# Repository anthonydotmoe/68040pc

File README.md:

# 68040pc

Welcome to the `68040pc` (working name) project, an ambitious endeavor to build
a general-purpose computer platform powered by the Motorola 68040 (or, in this
case, the 68LC040) CPU. Inspired by creations like Ben Eater's breadboard 6502
computer and me finding a 68LC040 in a bin, this project seeks to bring the
charm of vintage computing into the modern era with a twist of power and
utility. Call me crazy, but I expect to be able to use this machine when it's
done.

## Status

The `testboard` design is almost complete. I'm going to sleep on the design
before ordering boards. The FPGA does address decoding and interrupt
management and will contain a sound core to output some cool beeps through
the I2S DAC module. I'm pleased with how the project is going so far!

## Objectives

The `68040pc` aims to be versatile and user-friendly, with the following
capabilities:
- **Input/Output**: Support for keyboard (text input) and mouse for GUI
  interactions.
- **Display**: Text display for command-line operations and a graphics display
  ready for GUI applications.
- **Storage**: Compatibility with standard bulk storage devices, including
  floppies and hard drives.
- **OS**: Capability to run a preemptive multitasking operating system.
- **Expansion**: A robust expansion system, ensuring the platform remains
  relevant and adaptable after its initial production.

## Performance Expectations

With the integration of the 68040 CPU and the potential to accommodate up to
512MB of RAM, I anticipate the `68040pc` will rival the performance metrics of
systems like the Amiga, especially in terms of computational power. Although the
base system might not match the Amiga's graphical prowess, there's potential for
future enhancements via expansion cards to bring it to that level.

## Learning and Documentation

This journey isn't just about creating a new machine—it's a significant learning
curve for me, and I want it to serve as an educational resource for others.
Every step of the way, the system will be meticulously documented. From design
decisions to implementation nuances, the goal is to demystify the process and
make the knowledge accessible to all.

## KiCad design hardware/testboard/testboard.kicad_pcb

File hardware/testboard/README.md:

# Errata

* MC68150's TA line is *not* open-collector! Another 74LVC1G08 AND gate should
be used to connect FPGA TA and MC68150 TA to the CPU's TA.

* U802A schematic pin markings are incorrect. At the FPGA, the following changes
need to be made:
    - LV\_SIZ1 -> R/W
    - LV\_SIZ0 -> LV\_SIZ0
    - R/W -> LV\_SIZ1

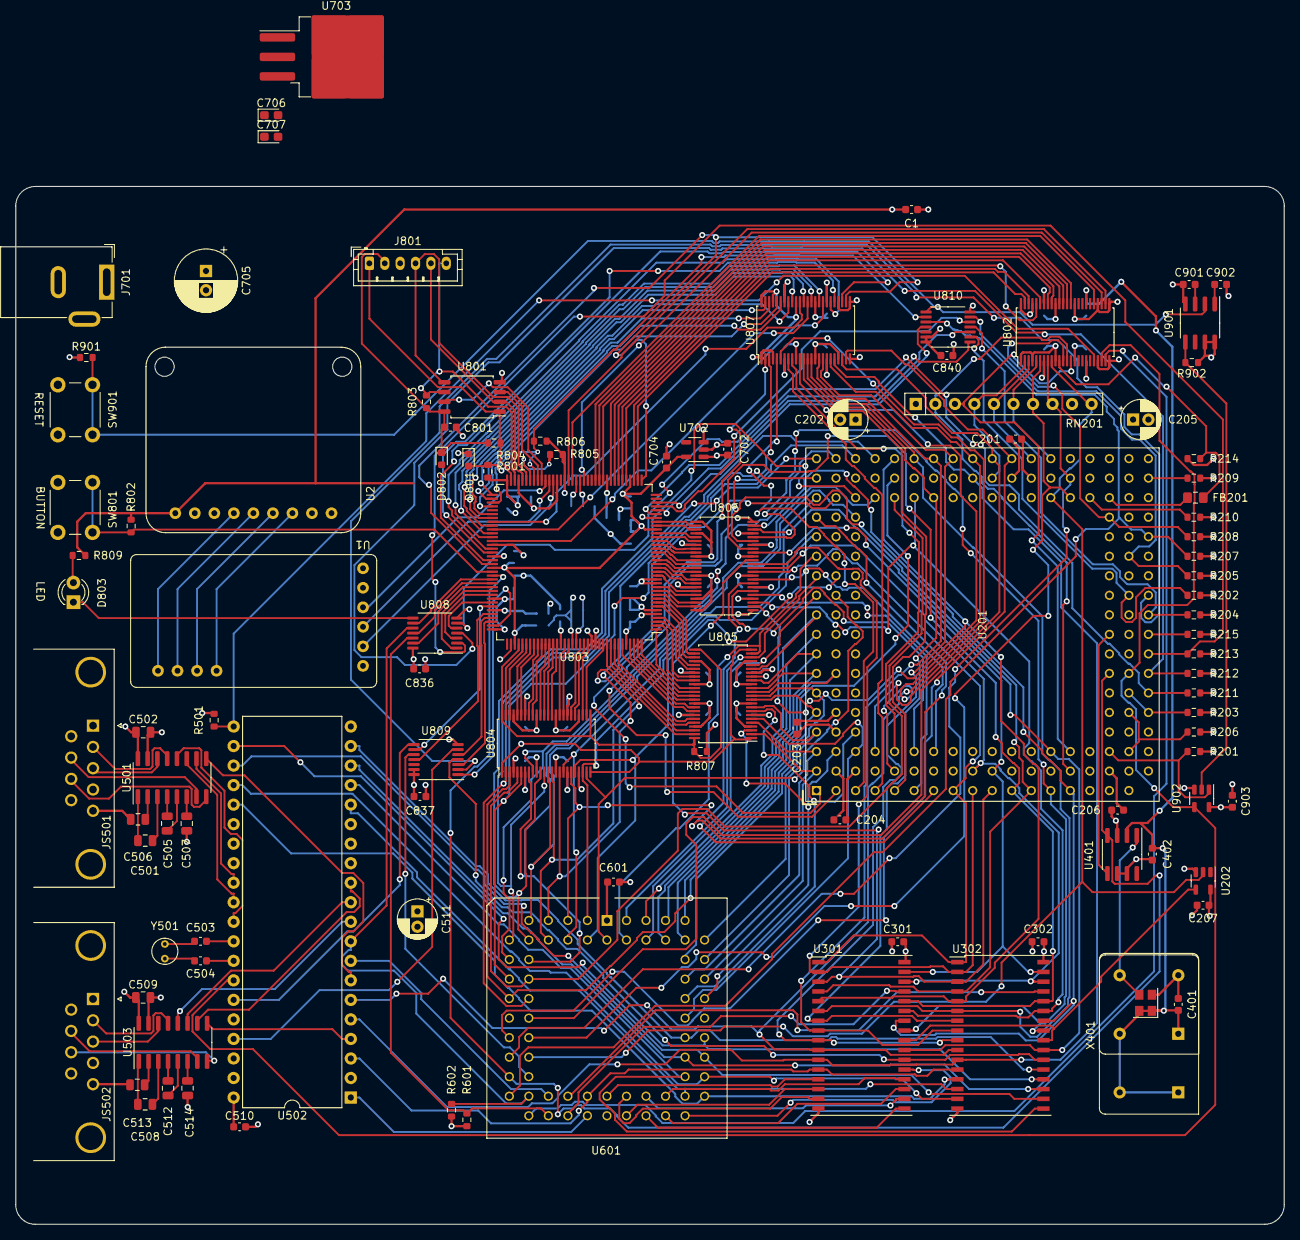
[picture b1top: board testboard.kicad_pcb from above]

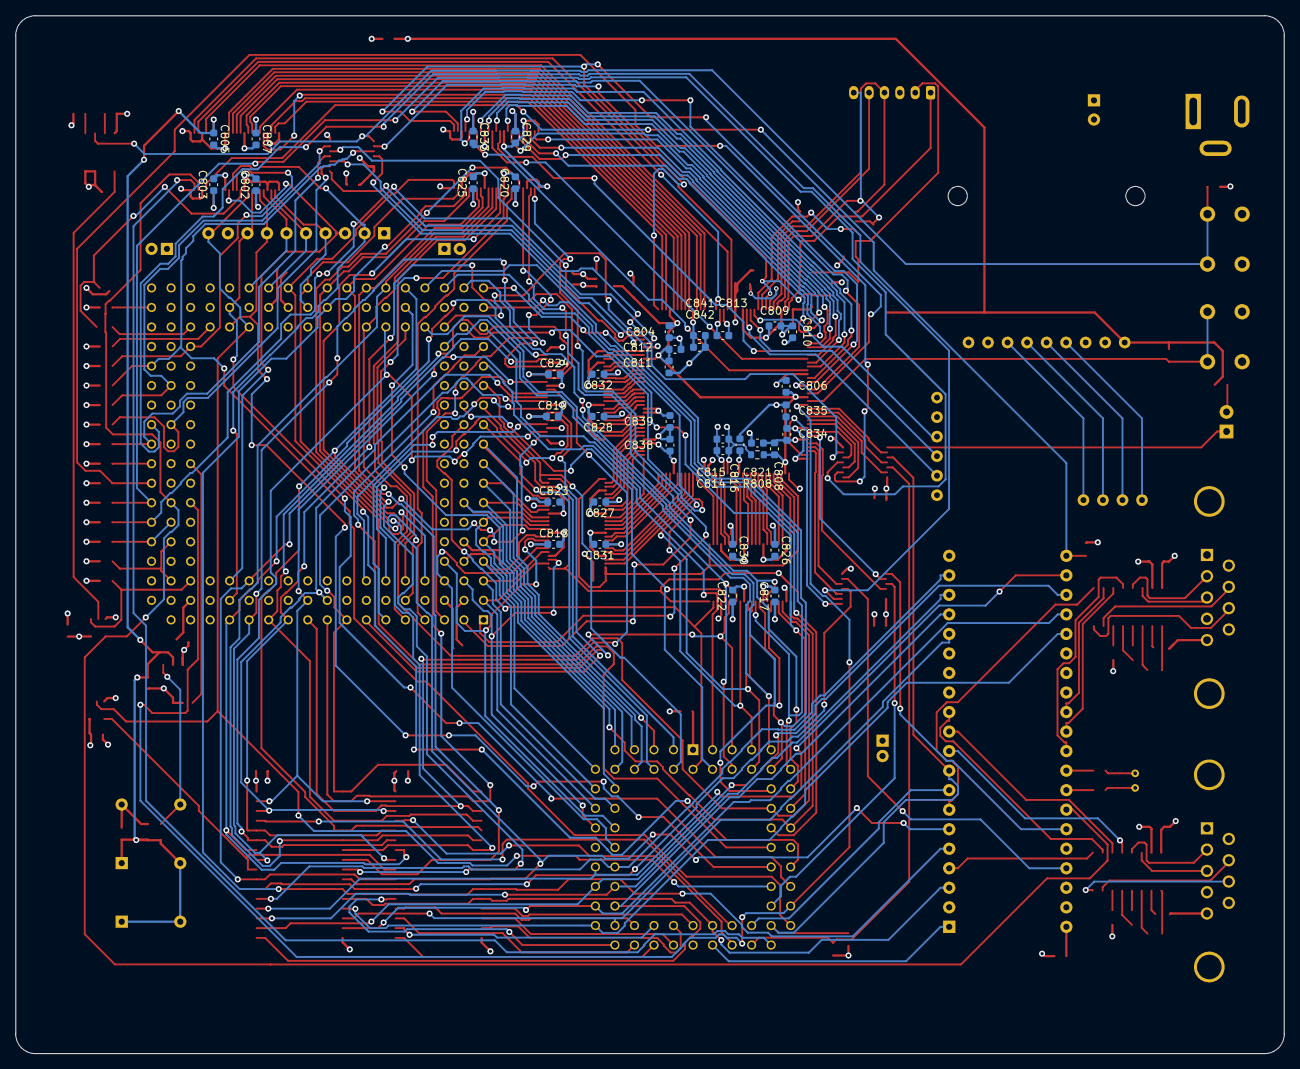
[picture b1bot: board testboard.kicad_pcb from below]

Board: 4 copper layers, 165.0 x 135.0 mm, 146 parts (39 on the bottom side), 278 nets.

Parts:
C1, C702, C704, C809, C812, C815, C821, C835, C839, C842: 4.7uF; C_0603_1608Metric
C201, C204: 0.22uF; C_0603_1608Metric
C202, C205: 22uF; CP_Radial_D5.0mm_P2.00mm
C203, C206: 220pF; C_0603_1608Metric
C207, C301, C302, C401, C402, C510, C601, C801, C802, C803, C804, C805, C806, C807, C808, C810, C811, C813, C814, C816, C817, C818, C819, C820, C822, C823, C824, C825, C826, C827, C828, C829, C830, C831, C832, C833, C834, C836, C837, C838, C840, C841, C901, C902, C903: 100nF; C_0603_1608Metric
C501, C502, C505, C506, C507, C508, C509, C512, C513, C514: 1uF; C_0805_2012Metric
C503, C504: 15pF; C_0603_1608Metric
C511: C_Polarized_Small_US; CP_Radial_D5.0mm_P2.00mm
C705: 220uF; CP_Radial_D8.0mm_P2.50mm
C706: 22uF; CP_EIA-2012-12_Kemet-R
C707: 10uF; CP_EIA-2012-12_Kemet-R
D801: LTST-C191KGKT; LED_0603_1608Metric
D802: D_Schottky; D_0603_1608Metric
D803: LED; LED_D3.0mm
FB201: FerriteBead; L_0805_2012Metric_Pad1.15x1.40mm_HandSolder
J701: Barrel_Jack; BarrelJack_GCT_DCJ200-10-A_Horizontal
J801: Conn_01x06; JST_PH_B6B-PH-K_1x06_P2.00mm_Vertical
JS501, JS502: DE9_Plug_MountingHoles; DSUB-9_Male_Horizontal_P2.77x2.84mm_EdgePinOffset4.94mm_Hou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
R201, R202, R203, R204, R205, R206, R207, R208, R209, R210, R211, R212, R213, R214, R215: 4.7k; R_0603_1608Metric
R501, R601, R602, R802, R901, R902: 1k; R_0603_1608Metric
R801, R809: 2.2K; R_0603_1608Metric
R803, R804: 10K; R_0603_1608Metric
R805, R806: 10k; R_0603_1608Metric
R807: R_Small_US; R_0603_1608Metric
R808: 100; R_0603_1608Metric
RN201: 1k; R_Array_SIP10
SW801: BUTTON; SW_PUSH_6mm
SW901: RESET; SW_PUSH_6mm
U1: DACMOD
U2: MAX98306 Amp; AMP
U201: 68LC040; PGA179
U202: 74LVC1G04; SOT-23-5
U301, U302: IS61C5128AS-25TLI; TSOP-II-32_21.0x10.2mm_P1.27mm
U401: NB3N502; SOIC-8_3.9x4.9mm_P1.27mm
U501, U503: MAX232; SOIC-16_3.9x9.9mm_P1.27mm
U502: 68681; DIP-40_W15.24mm
U601: PLCC-68_THT-Socket
U702: AP2112K-1.2; SOT-23-5
U703: LT1084-3.3; TO-263-3_TabPin2
U801: SST26VF023BA; SOP-8_5.28x5.23mm_P1.27mm
U802, U804, U805, U806, U807: SN74ALVC164245; TSSOP-48_6.1x12.5mm_P0.5mm
U803: ICE40HX4K-TQ144; TQFP-144_20x20mm_P0.5mm
U808, U810: SN74LVC07; TSSOP-14_4.4x5mm_P0.65mm
U809: 74AHCT04; TSSOP-14_4.4x5mm_P0.65mm
U901: TL7705A; SOIC-8_3.9x4.9mm_P1.27mm
U902: 74LVC1G08; SOT-23-5
X401: ASE-33MHz; Oscillator_SMD_Abracon_ASE-4Pin_3.2x2.5mm
X402: 33MHz; Oscillator_DIP-14
X403: 33MHz; Oscillator_DIP-8
Y501: 3.6864MHz; Crystal_C38-LF_D3.0mm_L8.0mm_Vertical

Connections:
+1V2: C704.1, C804.1, C806.1, C808.1, C811.1, C812.1, R808.2, U702.5 (VOUT), U803.27 (VCC), U803.40 (VCC), U803.92 (VCC), U803.111 (VCC)
+3.3V: C1.1, C401.1, C402.1, C706.1, C805.1, C807.1, C809.1, C810.1, C816.1, C821.1, C826.1, C827.1, C828.1, C829.1, C830.1, C831.1, C832.1, C833.1, C834.1, C835.1, C836.1, C838.1, C839.1, C840.1, C841.1, C842.1, D802.2 (A), R801.2, R802.1, R805.1, R806.1, R807.1, R809.2, U1.1 (VIN), U2.1 (V_{DD}), U401.2 (VDD), U703.2 (VO), U802.31 (VCCA), U802.42 (VCCA), U803.6 (VCCIO_3), U803.30 (VCCIO_3), U803.46 (VCCIO_2), U803.57 (VCCIO_2), U803.72 (VCC_SPI), U803.89 (VCCIO_1), U803.100 (VCCIO_1), U803.108 (VPP_2V5), U803.123 (VCCIO_0), U803.131 (VCCIO_0), U804.31 (VCCA), U804.42 (VCCA), U805.31 (VCCA), U805.42 (VCCA), U806.31 (VCCA), U806.42 (VCCA), U807.31 (VCCA), U807.42 (VCCA), U808.14 (VCC), U810.13, U810.14 (VCC), X401.1 (EN), X401.4 (Vdd), X402.1 (EN), X402.14 (Vcc), X403.1 (EN), X403.8 (Vcc)
+5V: C201.1, C202.1, C203.1, C204.1, C205.1, C206.1, C207.1, C301.1, C302.1, C502.1, C509.1, C510.1, C511.1, C601.1, C702.1, C705.1, C707.1, C802.1, C803.1, C817.1, C818.1, C819.1, C820.1, C822.1, C823.1, C824.1, C825.1, C837.1, C903.1, J701.1, R201.1, R202.1, R203.1, R204.1, R205.1, R206.1, R207.1, R208.1, R209.1, R210.1, R211.1, R212.1, R213.1, R214.1, R215.1, R501.1, R601.1, R602.1, R901.1, R902.1, RN201.1 (common), U201.B5 (V_{CC}), U201.B9 (V_{CC}), U201.B14 (V_{CC}), U201.C2 (V_{CC}), U201.C5 (V_{CC}), U201.C8 (V_{CC}), U201.C10 (V_{CC}), U201.C12 (V_{CC}), U201.C14 (V_{CC}), U201.C17 (V_{CC}), U201.G2 (V_{CC}), U201.G17 (V_{CC}), U201.H3 (V_{CC}), U201.H16 (V_{CC}), U201.J3 (V_{CC}), U201.J16 (V_{CC}), U201.L16 (V_{CC}), U201.M2 (V_{CC}), U201.M3 (V_{CC}), U201.M17 (V_{CC}), U201.R2 (V_{CC}), U201.R5 (V_{CC}), U201.R8 (V_{CC}), U201.R12 (V_{CC}), U201.R17 (V_{CC}), U201.S8 (V_{CC}), U201.S16 (V_{CC}), U202.5 (VCC), U301.32 (VDD), U302.32 (VDD), U501.16 (VCC), U502.40 (VCC), U503.16 (VCC), U601.1 (V_{CC}), U601.35 (V_{CC}), U702.1 (VIN), U702.3 (EN), U703.3 (VI), U802.7 (VCCB), U802.18 (VCCB), U804.7 (VCCB), U804.18 (VCCB), U805.7 (VCCB), U805.18 (VCCB), U806.7 (VCCB), U806.18 (VCCB), U807.7 (VCCB), U807.18 (VCCB), U809.13, U809.14 (VCC), U901.7 (SENSE), U901.8 (VCC), U902.5 (VCC)
/A0: U201.L18 (A0), U601.20 (A0), U807.23 (2B8)
/A1: U201.K18 (A1), U601.19 (A1), U807.22 (2B7)
/A2: U201.J17 (A2), U301.11 (A1), U302.11 (A1), U502.5 (RS3), U807.20 (2B6)
/A3: U201.J18 (A3), U301.10 (A2), U302.10 (A2), U502.6 (RS4), U807.19 (2B5)
/A4: U201.H18 (A4), U301.9 (A3), U302.9 (A3), U807.17 (2B4)
/A5: U201.G18 (A5), U301.8 (A4), U302.8 (A4), U807.16 (2B3)
/A6: U201.G16 (A6), U301.7 (A5), U302.7 (A5), U807.13 (2B1)
/A7: U201.F18 (A7), U301.6 (A6), U302.6 (A6), U807.14 (2B2)
/A8: U201.E18 (A8), U301.5 (A7), U302.5 (A7), U806.2 (1B1)
/A9: U201.F16 (A9), U301.27 (A8), U302.27 (A8), U806.3 (1B2)
/A10: U201.P1 (A10), U301.26 (A9), U302.26 (A9), U806.23 (2B8)
/A11: U201.N3 (A11), U301.23 (A10), U302.23 (A10), U806.22 (2B7)
/A12: U201.N1 (A12), U301.25 (A11), U302.25 (A11), U806.20 (2B6)
/A13: U201.M1 (A13), U301.4 (A12), U302.4 (A12), U806.19 (2B5)
/A14: U201.L1 (A14), U301.28 (A13), U302.28 (A13), U806.17 (2B4)
/A15: U201.K1 (A15), U301.3 (A14), U302.3 (A14), U806.14 (2B2)
/A16: U201.K2 (A16), U301.31 (A15), U302.31 (A15), U806.16 (2B3)
/A17: U201.J1 (A17), U301.2 (A16), U302.2 (A16), U806.13 (2B1)
/A18: U201.H1 (A18), U301.1 (A17), U302.1 (A17), U806.11 (1B7)
/A19: U201.J2 (A19), U301.30 (A18), U302.30 (A18), U806.12 (1B8)
/A20: U201.G1 (A20), U806.8 (1B5)
/A21: U201.F1 (A21), U806.5 (1B3)
/A22: U201.E1 (A22), U807.12 (1B8)
/A23: U201.G3 (A23), U806.9 (1B6)
/A24: U201.D1 (A24), U807.8 (1B5)
/A25: U201.F3 (A25), U806.6 (1B4)
/A26: U201.E2 (A26), U807.11 (1B7)
/A27: U201.C1 (A27), U807.5 (1B3)
/A28: U201.E3 (A28), U807.9 (1B6)
/A29: U201.B1 (A29), U807.3 (1B2)
/A30: U201.D3 (A30), U807.6 (1B4)
/A31: U201.A1 (A31), U807.2 (1B1)
/BCLK: U201.R7 (BCLK), U401.4 (REF), U601.24 (BCLK), U803.94 (IOR_141_GBIN2)
/CPU/DLE: R215.2, U201.T9 (JS0)
/CPU/PCLK: U201.R9 (PCLK), U401.5 (CLKOUT)
/CPU/~BB: R209.2, U201.T17 (~BB)
/CPU/~MI: R210.2, U201.Q16 (~MI)
/Clock/CLK33: U401.1 (X1/CLK), X401.3 (OUT), X403.5 (OUT)
/D0: U201.C3 (D0), U601.53 (D0), U805.6 (1B4)
/D1: U201.B3 (D1), U601.54 (D1), U805.3 (1B2)
/D2: U201.C4 (D2), U601.55 (D2), U805.8 (1B5)
/D3: U201.A2 (D3), U601.56 (D3), U805.2 (1B1)
/D4: U201.A3 (D4), U601.57 (D4), U805.5 (1B3)
/D5: U201.A4 (D5), U601.58 (D5), U805.9 (1B6)
/D6: U201.A5 (D6), U601.59 (D6), U805.11 (1B7)
/D7: U201.A6 (D7), U601.60 (D7), U805.12 (1B8)
/D8: U201.B7 (D8), U601.61 (D8), U805.13 (2B1)
/D9: U201.A7 (D9), U601.62 (D9), U805.14 (2B2)
/D10: U201.A8 (D10), U601.63 (D10), U805.16 (2B3)
/D11: U201.A9 (D11), U601.64 (D11), U805.17 (2B4)
/D12: U201.A10 (D12), U601.65 (D12), U805.19 (2B5)
/D13: U201.A11 (D13), U601.66 (D13), U805.20 (2B6)
/D14: U201.A12 (D14), U601.67 (D14), U805.22 (2B7)
/D15: U201.A13 (D15), U601.68 (D15), U805.23 (2B8)
/D16: U201.B11 (D16), U601.2 (D16), U804.23 (2B8)
/D17: U201.A14 (D17), U601.3 (D17), U804.22 (2B7)
/D18: U201.B12 (D18), U601.4 (D18), U804.20 (2B6)
/D19: U201.A15 (D19), U601.5 (D19), U804.19 (2B5)
/D20: U201.A16 (D20), U601.6 (D20), U804.17 (2B4)
/D21: U201.A17 (D21), U601.7 (D21), U804.16 (2B3)
/D22: U201.B16 (D22), U601.8 (D22), U804.14 (2B2)
/D23: U201.C15 (D23), U601.9 (D23), U804.13 (2B1)
/D24: U201.A18 (D24), U601.10 (D24), U804.12 (1B8)
/D25: U201.C16 (D25), U601.11 (D25), U804.11 (1B7)
/D26: U201.B18 (D26), U601.12 (D26), U804.9 (1B6)
/D27: U201.D16 (D27), U601.13 (D27), U804.8 (1B5)
/D28: U201.C18 (D28), U601.14 (D28), U804.6 (1B4)
/D29: U201.E16 (D29), U601.15 (D29), U804.5 (1B3)
/D30: U201.E17 (D30), U601.16 (D30), U804.3 (1B2)
/D31: U201.D18 (D31), U601.17 (D31), U804.2 (1B1)
/FPGA/CDONE: D801.2 (A), R801.1, R806.2, U803.65 (CDONE), U810.9
/FPGA/FLASH_IO2: U801.3 (~WP/SIO2), U803.64 (IOB_104_CBSEL1)
/FPGA/FLASH_IO3: U801.7 (~HOLD/SIO3), U803.63 (IOB_103_CBSEL0)
/FPGA/FLASH_MISO: J801.5, U801.2 (SO/SIO1), U803.68 (IOB_106_SDI)
/FPGA/FLASH_MOSI: J801.4, U801.5 (SI/SIO0), U803.67 (IOB_105_SDO)
/FPGA/FLASH_POWER: C801.1, D802.1 (K), J801.2, R803.2, R804.2, U801.8 (VCC)
/FPGA/FLASH_SCK: J801.6, R803.1, U801.6 (SCLK), U803.70 (IOB_107_SCK)
/FPGA/FLASH_SS: J801.1, R804.1, U801.1 (~CS), U803.71 (IOB_108_SS)
/FPGA/FPGA_BTN: R802.2, SW801.2, U803.93 (IOR_140_GBIN3)
/FPGA/FPGA_D_DIR: U803.110 (IOT_168), U804.1 (1DIR), U804.24 (2DIR), U805.1 (1DIR), U805.24 (2DIR)
/FPGA/FPGA_D_~OE: R807.2, U803.112 (IOT_169), U804.25 (*2OE), U804.48 (*1OE), U805.25 (*2OE), U805.48 (*1OE)
/FPGA/FPGA_LED: U803.95 (IOR_144), U808.9
/FPGA/GND_PLL: C813.2, C814.2, C815.2, U803.53 (GNDPLL0), U803.127 (GNDPLL1)
/FPGA/LV.A0: U803.37 (IOB_56), U803.91 (IOR_139), U807.26 (2A8)
/FPGA/LV.A1: U803.90 (IOR_138), U807.27 (2A7)
/FPGA/LV.A2: U803.88 (IOR_137), U807.29 (2A6)
/FPGA/LV.A3: U803.87 (IOR_136), U807.30 (2A5)
/FPGA/LV.A4: U803.85 (IOR_128), U807.32 (2A4)
/FPGA/LV.A5: U803.84 (IOR_120), U807.33 (2A3)
/FPGA/LV.A6: U803.82 (IOR_118), U807.36 (2A1)
/FPGA/LV.A7: U803.83 (IOR_119), U807.35 (2A2)
/FPGA/LV.A8: U803.10 (IOL_5B), U806.47 (1A1)
/FPGA/LV.A9: U803.11 (IOL_8A), U806.46 (1A2)
/FPGA/LV.A10: U803.29 (IOL_23B), U806.26 (2A8)
/FPGA/LV.A11: U803.28 (IOL_23A), U806.27 (2A7)
/FPGA/LV.A12: U803.26 (IOL_18B), U806.29 (2A6)
/FPGA/LV.A13: U803.25 (IOL_18A), U806.30 (2A5)
/FPGA/LV.A14: U803.24 (IOL_17B), U806.32 (2A4)
/FPGA/LV.A15: U803.22 (IOL_14B), U806.35 (2A2)
/FPGA/LV.A16: U803.23 (IOL_17A), U806.33 (2A3)
/FPGA/LV.A17: U803.21 (IOL_14A_GBIN6), U806.36 (2A1)
/FPGA/LV.A18: U803.18 (IOL_12B), U806.38 (1A7)
/FPGA/LV.A19: U803.19 (IOL_13A), U806.37 (1A8)
/FPGA/LV.A20: U803.16 (IOL_10B), U806.41 (1A5)
/FPGA/LV.A21: U803.12 (IOL_8B), U806.44 (1A3)
/FPGA/LV.A22: U803.81 (IOR_117), U807.37 (1A8)
/FPGA/LV.A23: U803.17 (IOL_12A), U806.40 (1A6)
/FPGA/LV.A24: U803.78 (IOR_114), U807.41 (1A5)
/FPGA/LV.A25: U803.15 (IOL_10A), U806.43 (1A4)
/FPGA/LV.A26: U803.80 (IOR_116), U807.38 (1A7)
/FPGA/LV.A27: U803.75 (IOR_111), U807.44 (1A3)
/FPGA/LV.A28: U803.79 (IOR_115), U807.40 (1A6)
/FPGA/LV.A29: U803.74 (IOR_110), U807.46 (1A2)
/FPGA/LV.A30: U803.76 (IOR_112), U807.43 (1A4)
/FPGA/LV.A31: U803.73 (IOR_109), U807.47 (1A1)
/FPGA/LV_68150_CS: U803.104 (IOR_164), U809.11
/FPGA/LV_AVEC: U803.107 (IOR_167), U809.1
/FPGA/LV_COM_CS: U803.102 (IOR_161), U809.9
/FPGA/LV_COM_IACK: U803.105 (IOR_165), U809.5
/FPGA/LV_D0: U803.138 (IOT_216), U805.43 (1A4)
/FPGA/LV_D1: U803.136 (IOT_214), U805.46 (1A2)
/FPGA/LV_D2: U803.139 (IOT_217), U805.41 (1A5)
/FPGA/LV_D3: U803.135 (IOT_213), U805.47 (1A1)
/FPGA/LV_D4: U803.137 (IOT_215), U805.44 (1A3)
/FPGA/LV_D5: U803.141 (IOT_219), U805.40 (1A6)
/FPGA/LV_D6: U803.142 (IOT_220), U805.38 (1A7)
/FPGA/LV_D7: U803.143 (IOT_221), U805.37 (1A8)
/FPGA/LV_D8: U803.144 (IOT_222), U805.36 (2A1)
/FPGA/LV_D9: U803.1 (IOL_2A), U805.35 (2A2)
/FPGA/LV_D10: U803.2 (IOL_2B), U805.33 (2A3)
/FPGA/LV_D11: U803.3 (IOL_3A), U805.32 (2A4)
/FPGA/LV_D12: U803.4 (IOL_3B), U805.30 (2A5)
/FPGA/LV_D13: U803.7 (IOL_4A), U805.29 (2A6)
/FPGA/LV_D14: U803.8 (IOL_4B), U805.27 (2A7)
/FPGA/LV_D15: U803.9 (IOL_5A), U805.26 (2A8)
/FPGA/LV_D16: U803.134 (IOT_212), U804.26 (2A8)
/FPGA/LV_D17: U803.130 (IOT_206), U804.27 (2A7)
/FPGA/LV_D18: U803.129 (IOT_198_GBIN0), U804.29 (2A6)
/FPGA/LV_D19: U803.128 (IOT_197_GBIN1), U804.30 (2A5)
/FPGA/LV_D20: U803.125 (IOT_192), U804.32 (2A4)
/FPGA/LV_D21: U803.124 (IOT_191), U804.33 (2A3)
/FPGA/LV_D22: U803.122 (IOT_190), U804.35 (2A2)
/FPGA/LV_D23: U803.121 (IOT_181), U804.36 (2A1)
/FPGA/LV_D24: U803.120 (IOT_179), U804.37 (1A8)
/FPGA/LV_D25: U803.119 (IOT_178), U804.38 (1A7)
/FPGA/LV_D26: U803.118 (IOT_177), U804.40 (1A6)
/FPGA/LV_D27: U803.117 (IOT_174), U804.41 (1A5)
/FPGA/LV_D28: U803.116 (IOT_173), U804.43 (1A4)
/FPGA/LV_D29: U803.115 (IOT_172), U804.44 (1A3)
/FPGA/LV_D30: U803.114 (IOT_171), U804.46 (1A2)
/FPGA/LV_D31: U803.113 (IOT_170), U804.47 (1A1)
/FPGA/LV_RAM_CS: U803.106 (IOR_166), U809.3
/FPGA/LV_R/~W: U802.43 (1A4), U803.42 (IOB_64)
/FPGA/LV_SIZ0: U802.41 (1A5), U803.43 (IOB_71)
/FPGA/LV_SIZ1: U802.40 (1A6), U803.44 (IOB_72)
/FPGA/LV_TM0: U802.44 (1A3), U803.41 (IOB_63)
/FPGA/LV_TM1: U802.46 (1A2), U803.39 (IOB_61)
/FPGA/LV_TM2: U802.47 (1A1), U803.38 (IOB_57)
/FPGA/LV_TT0: U802.35 (2A2), U803.49 (IOB_81_GBIN5)
/FPGA/LV_TT1: U802.36 (2A1), U803.48 (IOB_80)
/FPGA/LV_~68150_DS: U802.26 (2A8), U803.56 (IOB_94)
/FPGA/LV_~COM_IRQ: U802.29 (2A6), U803.55 (IOB_91)
/FPGA/LV_~DSACK0: U803.96 (IOR_146), U808.11
/FPGA/LV_~DSACK1: U803.97 (IOR_147), U808.13
/FPGA/LV_~IPL0: U803.98 (IOR_148), U808.1
/FPGA/LV_~IPL1: U803.99 (IOR_152), U808.3
/FPGA/LV_~IPL2: U803.101 (IOR_160), U808.5
/FPGA/LV_~RST: U802.27 (2A7), U803.52 (IOB_82_GBIN4)
/FPGA/LV_~TA: U803.34 (IOL_25B), U810.11
/FPGA/LV_~TBI: U803.31 (IOL_24A), U810.1
/FPGA/LV_~TCI: U803.32 (IOL_24B), U810.3
/FPGA/LV_~TEA: U803.33 (IOL_25A), U810.5
/FPGA/LV_~TIP: U802.37 (1A8), U803.47 (IOB_79)
/FPGA/LV_~TS: U802.38 (1A7), U803.45 (IOB_73)
/FPGA/SND_BCLK: U1.5 (BCK), U803.60 (IOB_95)
/FPGA/SND_DOUT: U1.4 (DIN), U803.61 (IOB_96)
/FPGA/SND_LRCLK: U1.3 (LRCLK), U803.62 (IOB_102)
/FPGA/VCC_PLL: C813.1, C814.1, C815.1, R808.1, U803.54 (VCCPLL0), U803.126 (VCCPLL1)
/IO/A_RX: U501.12 (R1OUT), U502.31 (RXDA)
/IO/A_TX: U501.11 (T1IN), U502.30 (TXDA)
/IO/A_~CTS: U501.9 (R2OUT), U502.7 (IP0)
/IO/A_~RTS: U501.10 (T2IN), U502.29 (OP0)
/IO/B_RX: U502.10 (RXDB), U503.12 (R1OUT)
/IO/B_TX: U502.11 (TXDB), U503.11 (T1IN)
/IO/B_~CTS: U502.4 (IP1), U503.9 (R2OUT)
/IO/B_~RTS: U502.12 (OP1), U503.10 (T2IN)
/IO/COM1_CTS: JS501.8, U501.8 (R2IN)
/IO/COM1_RTS: JS501.7, U501.7 (T2OUT)
/IO/COM1_RXD: JS501.2, U501.13 (R1IN)
/IO/COM1_TXD: JS501.3, U501.14 (T1OUT)
/IO/COM2_CTS: JS502.8, U503.8 (R2IN)
/IO/COM2_RTS: JS502.7, U503.7 (T2OUT)
/IO/COM2_RXD: JS502.2, U503.13 (R1IN)
/IO/COM2_TXD: JS502.3, U503.14 (T1OUT)
/PA0: U502.1 (RS1), U601.33 (PA0)
/PA1: U301.12 (A0), U302.12 (A0), U502.3 (RS2), U601.34 (PA1)
/PD16: U301.13 (I/O0), U601.36 (PD16)
/PD17: U301.14 (I/O1), U601.37 (PD17)
/PD18: U301.15 (I/O2), U601.38 (PD18)
/PD19: U301.17 (I/O3), U601.39 (PD19)
/PD20: U301.18 (I/O4), U601.40 (PD20)
/PD21: U301.19 (I/O5), U601.41 (PD21)
/PD22: U301.20 (I/O6), U601.42 (PD22)
/PD23: U301.21 (I/O7), U601.43 (PD23)
/PD24: U302.13 (I/O0), U502.25 (D0), U601.44 (PD24)
/PD25: U302.14 (I/O1), U502.16 (D1), U601.45 (PD25)
/PD26: U302.15 (I/O2), U502.24 (D2), U601.46 (PD26)
/PD27: U302.17 (I/O3), U502.17 (D3), U601.47 (PD27)
/PD28: U302.18 (I/O4), U502.23 (D4), U601.48 (PD28)
/PD29: U302.19 (I/O5), U502.18 (D5), U601.49 (PD29)
/PD30: U302.20 (I/O6), U502.22 (D6), U601.50 (PD30)
/PD31: U302.21 (I/O7), U502.19 (D7), U601.51 (PD31)
/Reset/HW_RST: R902.2, U901.5 (~RESET), U902.2
/R/~W: RN201.10 (R9), U201.N16 (R/~W), U202.2, U601.23 (R/~W), U802.9 (1B6)
/SIZ0: RN201.8 (R7), U201.P17 (SIZ0), U601.22 (SIZ0), U802.8 (1B5)
/SIZ1: RN201.7 (R6), U201.P16 (SIZ1), U601.21 (SIZ1), U802.6 (1B4)
/TM0: RN201.6 (R5), U201.N18 (TM0), U802.5 (1B3)
/TM1: RN201.5 (R4), U201.M18 (TM1), U802.3 (1B2)
/TM2: RN201.4 (R3), U201.K17 (TM2), U802.2 (1B1)
/TT0: RN201.3 (R2), U201.P3 (TT0), U802.14 (2B2)
/TT1: RN201.2 (R1), U201.P2 (TT1), U802.13 (2B1)
/~68150_CS: U601.25 (~CS), U809.10
/~AVEC: U201.T11 (~AVEC), U809.2
/~COM_CS: U502.35 (CS), U809.8
/~COM_IACK: U502.37 (IACK), U809.6
/~COM_IRQ: R501.2, U502.21 (IRQ), U802.20 (2B6)
/~DSACK0: R602.2, U502.9 (DTACK), U601.28 (~DSACK0), U808.10
/~DSACK1: R601.2, U601.29 (~DSACK1), U808.12
/~DS: U601.27 (~DS), U802.23 (2B8)
/~FPGA_WAIT: R901.2, SW901.2, U810.8, U901.2 (~RESIN)
/~IPL0: R213.2, U201.T8 (~IPL0), U808.2
/~IPL1: R212.2, U201.T7 (~IPL1), U808.4
/~IPL2: R211.2, U201.T6 (~IPL2), U808.6
/~LWE: U301.29 (~WE), U601.31 (~LWE)
/~RAM_CS: U301.22 (~CE), U302.22 (~CE), U809.4
/~RST: U201.S7 (~RSTI), U502.34 (RESET), U802.22 (2B7), U902.4
/~R/W: U202.4, U301.24 (~OE), U302.24 (~OE)
/~SWE: U502.8 (R/W), U601.30 (~SWE)
/~SW_RST: R201.2, U201.R3 (~RSTO), U902.1
/~TA: R207.2, U201.T14 (~TA), U601.26 (~TA), U810.10
/~TBI: R202.2, U201.S11 (~TBI), U810.2
/~TCI: R204.2, U201.T10 (~TCI), U810.4
/~TEA: R205.2, U201.S13 (~TEA), U810.6
/~TIP: R208.2, U201.R15 (~TIP), U802.12 (1B8)
/~TS: FB201.2, R214.2, U802.11 (1B7)
/~UWE: U302.29 (~WE), U601.32 (~UWE)
GND: C1.2, C201.2, C202.2, C203.2, C204.2, C205.2, C206.2, C207.2, C301.2, C302.2, C401.2, C402.2, C502.2, C506.2, C507.2, C509.2, C510.2, C511.2, C513.2, C514.2, C601.2, C702.2, C704.2, C705.2, C706.2, C707.2, C801.2, C802.2, C803.2, C804.2, C805.2, C806.2, C807.2, C808.2, C809.2, C810.2, C811.2, C812.2, C816.2, C817.2, C818.2, C819.2, C820.2, C821.2, C822.2, C823.2, C824.2, C825.2, C826.2, C827.2, C828.2, C829.2, C830.2, C831.2, C832.2, C833.2, C834.2, C835.2, C836.2, C837.2, C838.2, C839.2, C840.2, C841.2, C842.2, C901.2, C902.2, C903.2, D801.1 (K), J701.2, J801.3, JS501.0 (PAD), JS501.5, JS502.0 (PAD), JS502.5, SW801.1, SW901.1, U1.2 (GND), U2.2 (GND), U201.B2 (GND), U201.B4 (GND), U201.B6 (GND), U201.B8 (GND), U201.B10 (GND), U201.B13 (GND), U201.B15 (GND), U201.B17 (GND), U201.C6 (GND), U201.C7 (GND), U201.C9 (GND), U201.C11 (GND), U201.C13 (GND), U201.D2 (GND), U201.D17 (GND), U201.F2 (GND), U201.F17 (GND), U201.H2 (GND), U201.H17 (GND), U201.K3 (GND), U201.K16 (GND), U201.L2 (GND), U201.L3 (GND), U201.L17 (GND), U201.M16 (GND), U201.N2 (GND), U201.N17 (GND), U201.Q2 (GND), U201.Q17 (GND), U201.R4 (GND), U201.R6 (GND), U201.R10 (GND), U201.R11 (GND), U201.R13 (GND), U201.S2 (GND), U201.S4 (TCK), U201.S9 (GND), U201.S10 (GND), U201.S12 (SC1), U201.S15 (GND), U201.S17 (GND), U201.T3 (~TRST), U201.T4 (GND), U201.T12 (SC0), U201.T13 (~BG), U202.3 (GND), U301.16 (GND), U302.16 (GND), U401.3 (GND), U401.6 (S0), U401.7 (S1), U501.15 (GND), U502.20 (GND), U503.15 (GND), U601.18 (GND), U601.52 (GND), U702.2 (GND), U703.1 (GND), U801.4 (GND), U802.1 (1DIR), U802.4 (GND), U802.10 (GND), U802.15 (GND), U802.21 (GND), U802.24 (2DIR), U802.25 (*2OE), U802.28 (GND), U802.34 (GND), U802.39 (GND), U802.45 (GND), U802.48 (*1OE), U803.5 (GND), U803.13 (GND), U803.14 (GND), U803.59 (GND), U803.69 (GND), U803.86 (GND), U803.103 (GND), U803.132 (GND), U803.140 (GND), U804.4 (GND), U804.10 (GND), U804.15 (GND), U804.21 (GND), U804.28 (GND), U804.34 (GND), U804.39 (GND), U804.45 (GND), U805.4 (GND), U805.10 (GND), U805.15 (GND), U805.21 (GND), U805.28 (GND), U805.34 (GND), U805.39 (GND), U805.45 (GND), U806.1 (1DIR), U806.4 (GND), U806.10 (GND), U806.15 (GND), U806.21 (GND), U806.24 (2DIR), U806.25 (*2OE), U806.28 (GND), U806.34 (GND), U806.39 (GND), U806.45 (GND), U806.48 (*1OE), U807.1 (1DIR), U807.4 (GND), U807.10 (GND), U807.15 (GND), U807.21 (GND), U807.24 (2DIR), U807.25 (*2OE), U807.28 (GND), U807.34 (GND), U807.39 (GND), U807.45 (GND), U807.48 (*1OE), U808.7 (GND), U809.7 (GND), U810.7 (GND), U901.4 (GND), U902.3 (GND), X401.2 (GND), X403.4 (GND)
unnamed: C503.1, Y501.1
unnamed: C504.1, Y501.2
unnamed: D803.2 (A), R809.1
unnamed: D803.1 (K), U808.8
unnamed: U1.7 (L), U2.4 (L+)
unnamed: U1.9 (R), U2.6 (R+)
unnamed: U1.8 (G), U2.5 (L-)
unnamed: U1.10 (G), U2.7 (R-)
unnamed: R206.2, U201.S3 (TDI), U201.S5 (TMS)
unnamed: R203.2, U201.S6 (~MDIS), U201.T5 (~CDIS)
unnamed: FB201.1, U201.R16 (~TS)
unnamed: C501.1, U501.1 (C1+)
unnamed: C501.2, U501.3 (C1-)
unnamed: C505.1, U501.4 (C2+)
unnamed: C505.2, U501.5 (C2-)
unnamed: C506.1, U501.2 (VS+)
unnamed: C507.1, U501.6 (VS-)
unnamed: C503.2, U502.32 (X1/CLK)
unnamed: C504.2, U502.33 (X2)
unnamed: C508.1, U503.1 (C1+)
unnamed: C508.2, U503.3 (C1-)
unnamed: C512.1, U503.4 (C2+)
unnamed: C512.2, U503.5 (C2-)
unnamed: C513.1, U503.2 (VS+)
unnamed: C514.1, U503.6 (VS-)
unnamed: R805.2, U803.66 (~CRESET)
unnamed: C901.1, U901.3 (CT)
unnamed: C902.1, U901.1 (REF)

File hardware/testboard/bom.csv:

Reference,Value,JLCPCB,Footprint,Datasheet,Qty
"C1, C701-C704, C809, C812, C815, C821, C835, C839, C842",4.7uF,,Capacitor_SMD:C_0603_1608Metric,~,12
"C201, C204",0.22uF,,Capacitor_SMD:C_0603_1608Metric,~,2
"C202, C205",22uF,,Capacitor_THT:CP_Radial_D5.0mm_P2.00mm,~,2
"C203, C206",220pF,,Capacitor_SMD:C_0603_1608Metric,~,2
"C207, C301, C302, C401, C402, C510, C601, C801-C808, C810, C811, C813, C814, C816-C820, C822-C834, C836-C838, C840, C841, C901-C903",100nF,,Capacitor_SMD:C_0603_1608Metric,~,45
"C501, C502, C505-C509, C512-C514",1uF,,Capacitor_SMD:C_0805_2012Metric,~,10
"C503, C504",15pF,,Capacitor_SMD:C_0603_1608Metric,~,2
C511,C_Polarized_Small_US,,Capacitor_THT:CP_Radial_D5.0mm_P2.00mm,~,1
C705,220uF,,Capacitor_THT:CP_Radial_D8.0mm_P2.50mm,~,1
D801,LTST-C191KGKT,C125098,LED_SMD:LED_0603_1608Metric,~,1
D802,D_Schottky,C2886023,Diode_SMD:D_0603_1608Metric,~,1
D803,LED,,LED_THT:LED_D3.0mm,~,1
FB201,FerriteBead,,Inductor_SMD:L_0805_2012Metric_Pad1.15x1.40mm_HandSolder,~,1
J701,Barrel_Jack,,Connector_BarrelJack:BarrelJack_GCT_DCJ200-10-A_Horizontal,~,1
J801,Conn_01x06,,Connector_JST:JST_PH_B6B-PH-K_1x06_P2.00mm_Vertical,~,1
"JS501, JS502",DE9_Plug_MountingHoles,,Connector_Dsub:DSUB-9_Male_Horizontal_P2.77x2.84mm_EdgePinOffset4.94mm_Housed_MountingHolesOffset7.48mm, ~,2
R201-R215,4.7k,,Resistor_SMD:R_0603_1608Metric,~,15
"R501, R601, R602, R802, R901, R902",1k,,Resistor_SMD:R_0603_1608Metric,~,6
"R801, R809",2.2K,,Resistor_SMD:R_0603_1608Metric,~,2
"R803, R804",10K,,Resistor_SMD:R_0603_1608Metric,~,2
"R805, R806",10k,,Resistor_SMD:R_0603_1608Metric,~,2
R807,R_Small_US,,Resistor_SMD:R_0603_1608Metric,~,1
R808,100,,Resistor_SMD:R_0603_1608Metric,~,1
RN201,1k,,Resistor_THT:R_Array_SIP10,http://www.vishay.com/docs/31509/csc.pdf,1
SW801,BUTTON,,Button_Switch_THT:SW_PUSH_6mm,~,1
SW901,RESET,,Button_Switch_THT:SW_PUSH_6mm,~,1
U1,~,,68040:DACMOD,,1
U2,MAX98306 Amp,,68040:AMP,,1
U201,68LC040,,68040:PGA179,,1
U202,74LVC1G04,C7827,Package_TO_SOT_SMD:SOT-23-5,https://www.ti.com/lit/ds/symlink/sn74lvc1g04.pdf,1
"U301, U302",IS61C5128AS-25TLI,,Package_SO:TSOP-II-32_21.0x10.2mm_P1.27mm,http://www.issi.com/WW/pdf/61-64C5128AL.pdf,2
U401,NB3N502,C462878,Package_SO:SOIC-8_3.9x4.9mm_P1.27mm,https://www.onsemi.com/download/data-sheet/pdf/nb3n502-d.pdf,1
"U501, U503",MAX232,C59824,Package_SO:SOIC-16_3.9x9.9mm_P1.27mm,http://www.ti.com/lit/ds/symlink/max232.pdf,2
U502,68681,,Package_DIP:DIP-40_W15.24mm,,1
U601,~,,Package_LCC:PLCC-68_THT-Socket,,1
U701,AP2112K-3.3,C51118,Package_TO_SOT_SMD:SOT-23-5,https://www.diodes.com/assets/Datasheets/AP2112.pdf,1
U702,AP2112K-1.2,NO STOCK,Package_TO_SOT_SMD:SOT-23-5,https://www.diodes.com/assets/Datasheets/AP2112.pdf,1
U801,SST26VF023BA,,Package_SO:SOP-8_5.28x5.23mm_P1.27mm,"https://www.macronix.com/Lists/Datasheet/Attachments/8377/MX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,%203V,%2032Mb,%20v1.1.pdf",1
"U802, U804-U807",SN74ALVC164245,C3755042,Package_SO:TSSOP-48_6.1x12.5mm_P0.5mm,SN74ALVC164245DLR,5
U803,ICE40HX4K-TQ144,C1521989,Package_QFP:TQFP-144_20x20mm_P0.5mm,http://www.latticesemi.com/Products/FPGAandCPLD/iCE40,1
"U808, U810",SN74LVC07,C7809,Package_SO:TSSOP-14_4.4x5mm_P0.65mm,https://www.ti.com/lit/ds/symlink/sn74lvc07a.pdf,2
U809,74AHCT04,C554474,Package_SO:TSSOP-14_4.4x5mm_P0.65mm,https://assets.nexperia.com/documents/data-sheet/74AHC_AHCT04.pdf,1
U901,TL7705A,C350569,Package_SO:SOIC-8_3.9x4.9mm_P1.27mm,http://www.ti.com.cn/cn/lit/ds/symlink/tl7705a.pdf,1
U902,74LVC1G08,C7666,Package_TO_SOT_SMD:SOT-23-5,https://www.ti.com/lit/ds/symlink/sn74lvc1g08.pdf,1
X401,ASE-33MHz,,Oscillator:Oscillator_SMD_Abracon_ASE-4Pin_3.2x2.5mm,http://www.abracon.com/Oscillators/ASV.pdf,1
X402,33MHz,,Oscillator:Oscillator_DIP-14,http://cdn-reichelt.de/documents/datenblatt/B400/OSZI.pdf,1
X403,33MHz,,Oscillator:Oscillator_DIP-8,http://cdn-reichelt.de/documents/datenblatt/B400/OSZI.pdf,1
Y501,3.6864MHz,,Crystal:Crystal_C38-LF_D3.0mm_L8.0mm_Vertical,~,1
